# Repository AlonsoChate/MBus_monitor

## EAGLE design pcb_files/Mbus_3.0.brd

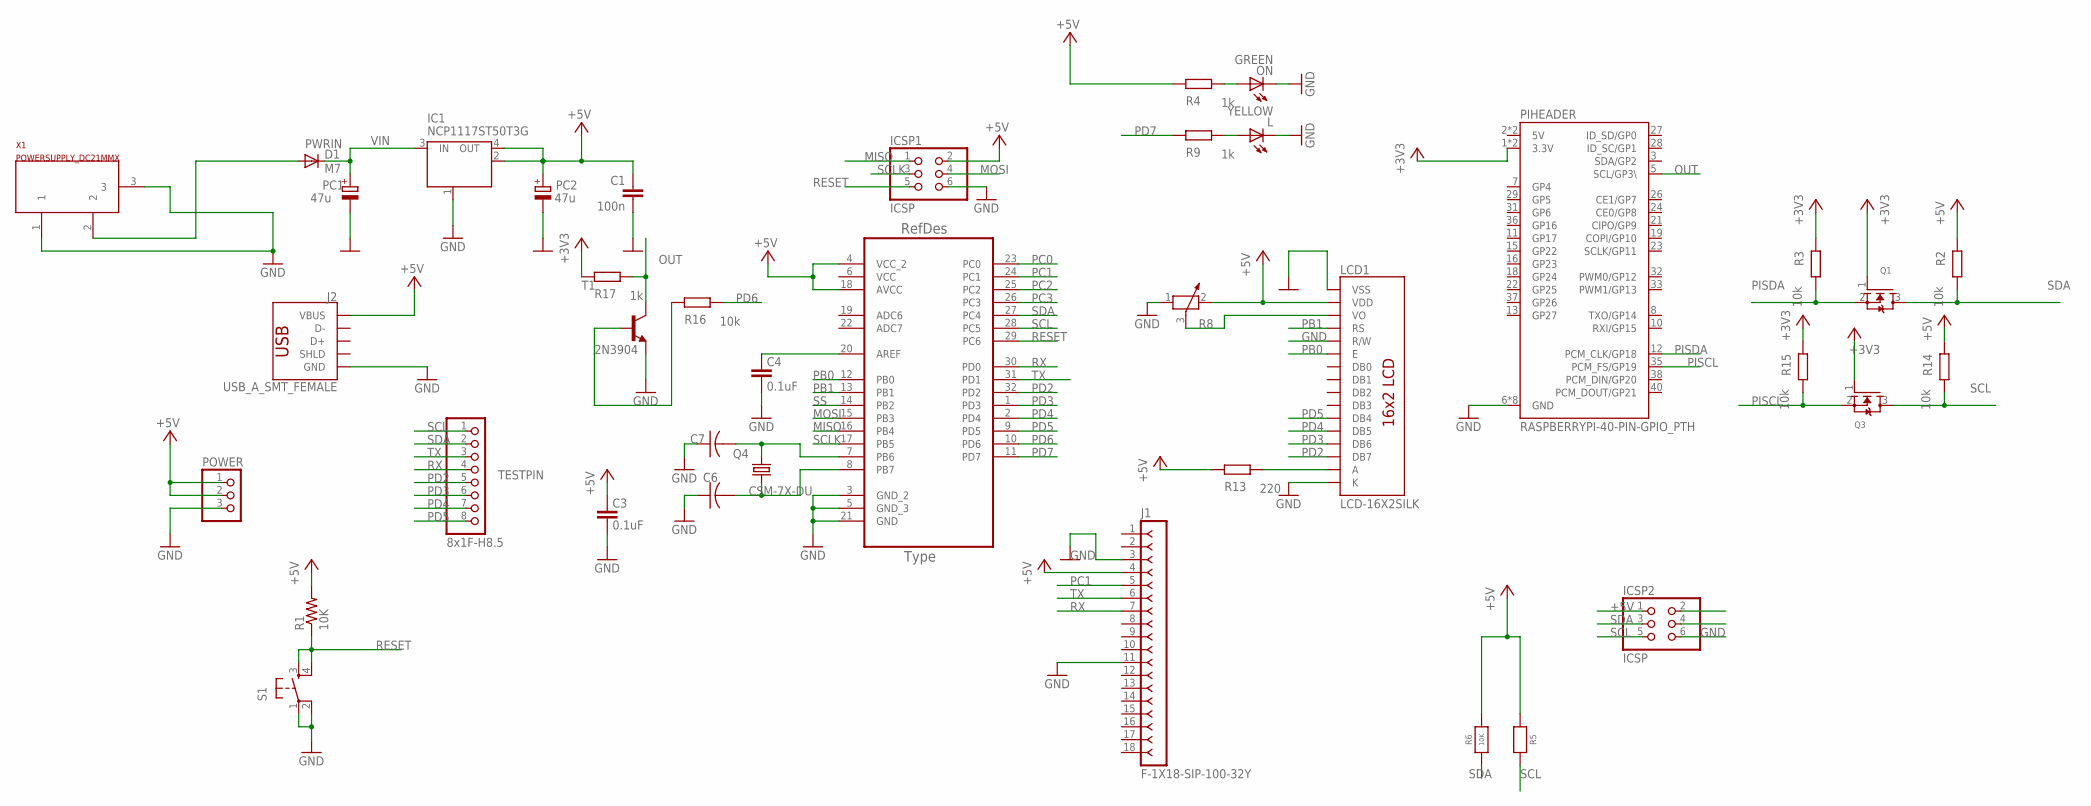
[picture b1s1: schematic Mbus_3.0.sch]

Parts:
C1: 100n; C0603-ROUND
C3, C4: 0.1uF; 0805
C6, C7: C-USC0805; C0805
D1: M7; SMB
IC1: NCP1117ST50T3G; SOT223
ICSP1, ICSP2: ICSP; 2X03
J1: F-1X18-SIP-100-32Y; SIP-100-18-32Y
J2: USB_A_SMT_FEMALE; USB-A-S-SILK-FEMALE
L: YELLOW; CHIP-LED0805
LCD1: LCD-16X2SILK; LCD-16X2
ON: GREEN; CHIP-LED0805
PC1, PC2: 47u; PANASONIC_D
PIHEADER: RASPBERRYPI-40-PIN-GPIO_PTH; 2X20_SHROUDED
POWER: PINHD-1X3; 1X03
Q1, Q3: BSS138; SOT23
Q4: CSM-7X-DU
R1: 10K; 0805
R2, R3, R14, R15, R16: 10k; R0603-ROUND
R4, R9, R17: 1k; R0603-ROUND
R5, R6: 10K; 0805-NO
R8: POTENTIOMETER_PT-10; PT-10
R13: 220; R0603-ROUND
S1: TAC_SWITCHPTH; TACTILE-PTH
T1: 2N3904; TO92
TESTPIN: 8x1F-H8.5; 1X08
U1: ATMEGA328P-AU; QFP80P900X900X120-32N
X1: POWERSUPPLY_DC21MMX; POWERSUPPLY_DC-21MM

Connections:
5V: PIHEADER.2 (5V), PIHEADER.4 (5V)
+3V3: PIHEADER.1 (3.3V), PIHEADER.17 (3.3V), Q1.1 (G), Q3.1 (G), R3.2, R15.2, R17.2
+5V: C1.1, C3.2, IC1.2 (OUT), IC1.4 (OUT), ICSP1.2, ICSP2.1, J1.4, J2.VBUS, LCD1.2 (VDD), PC2.+, POWER.1, POWER.2, R1.2, R2.2, R4.2, R5.1, R6.2, R8.2, R13.2, R14.2, U1.4 (VCC_2), U1.18 (AVCC)
GND: C1.2, C3.1, C4.1, C6.1, C7.1, IC1.1 (GND/ADJ), ICSP1.6, ICSP2.6, J1.3, J1.11, J2.GND, L.C, LCD1.1 (VSS), LCD1.5 (R/W), LCD1.16 (K), ON.C, PC1.-, PC2.-, PIHEADER.6 (GND), PIHEADER.9 (GND), PIHEADER.14 (GND), PIHEADER.20 (GND), PIHEADER.25 (GND), PIHEADER.30 (GND), PIHEADER.34 (GND), PIHEADER.39 (GND), POWER.3, R8.1, S1.1, S1.2, T1.3 (E), U1.3 (GND_2), U1.5 (GND_3), U1.21 (GND), X1.1, X1.3
MISO: ICSP1.1, U1.16 (PB4)
MOSI: ICSP1.4, U1.15 (PB3)
unnamed: C6.2, Q4.1, U1.8 (PB7)
unnamed: L.A, R9.1
unnamed: ON.A, R4.1
unnamed: R16.2, T1.2 (B)
unnamed: LCD1.15 (A), R13.1
unnamed: C7.2, Q4.2, U1.7 (PB6)
unnamed: C4.2, U1.20 (AREF)
unnamed: LCD1.3 (VO), R8.3
OUT: PIHEADER.5 (SCL/GP3\), R17.1, T1.1 (C)
PB0: LCD1.6 (E), U1.12 (PB0)
PB1: LCD1.4 (RS), U1.13 (PB1)
PC0: U1.23 (PC0)
PC1: J1.5, U1.24 (PC1)
PC2: U1.25 (PC2)
PC3: U1.26 (PC3)
PD2: LCD1.14 (DB7), TESTPIN.5, U1.32 (PD2)
PD3: LCD1.13 (DB6), TESTPIN.6, U1.1 (PD3)
PD4: LCD1.12 (DB5), TESTPIN.7, U1.2 (PD4)
PD5: LCD1.11 (DB4), TESTPIN.8, U1.9 (PD5)
PD6: R16.1, U1.10 (PD6)
PD7: R9.2, U1.11 (PD7)
PISCL: PIHEADER.35 (PCM_FS/GP19), Q3.2 (S), R15.1
PISDA: PIHEADER.12 (PCM_CLK/GP18), Q1.2 (S), R3.1
PWRIN: D1.A, X1.2
RESET: ICSP1.5, R1.1, S1.3, S1.4, U1.29 (PC6)
RX: J1.7, TESTPIN.4, U1.30 (PD0)
SCL: ICSP2.5, Q3.3 (D), R5.2, R14.1, TESTPIN.1, U1.28 (PC5)
SCLK: ICSP1.3, U1.17 (PB5)
SDA: ICSP2.3, Q1.3 (D), R2.1, R6.1, TESTPIN.2, U1.27 (PC4)
SS: U1.14 (PB2)
TX: J1.6, TESTPIN.3, U1.31 (PD1)
VCC: U1.6 (VCC)
VIN: D1.C, IC1.3 (IN), PC1.+

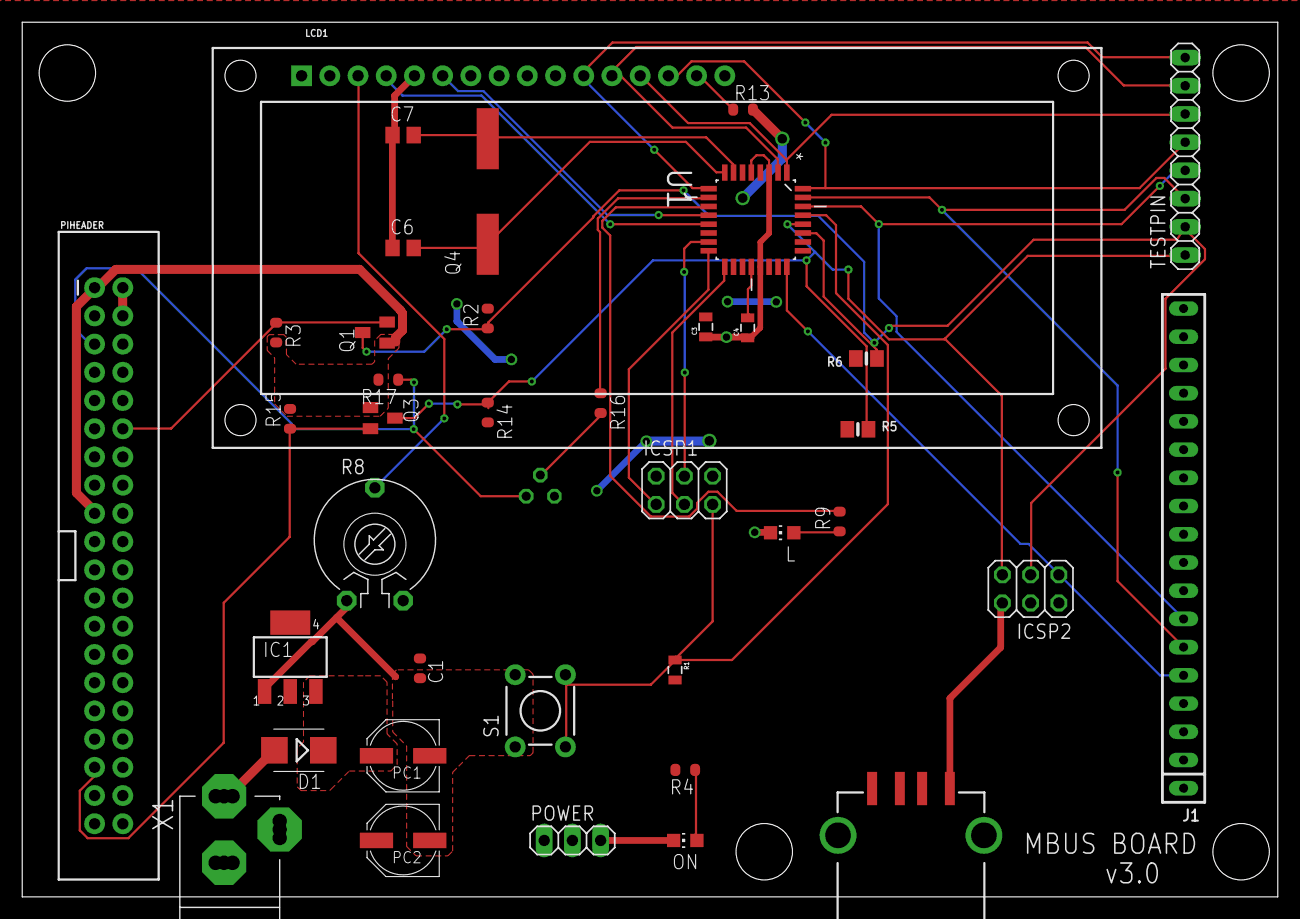
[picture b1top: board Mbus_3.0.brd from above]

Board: 2 copper layers, 113.0 x 78.7 mm, 39 parts (1 on the bottom side), 34 nets.

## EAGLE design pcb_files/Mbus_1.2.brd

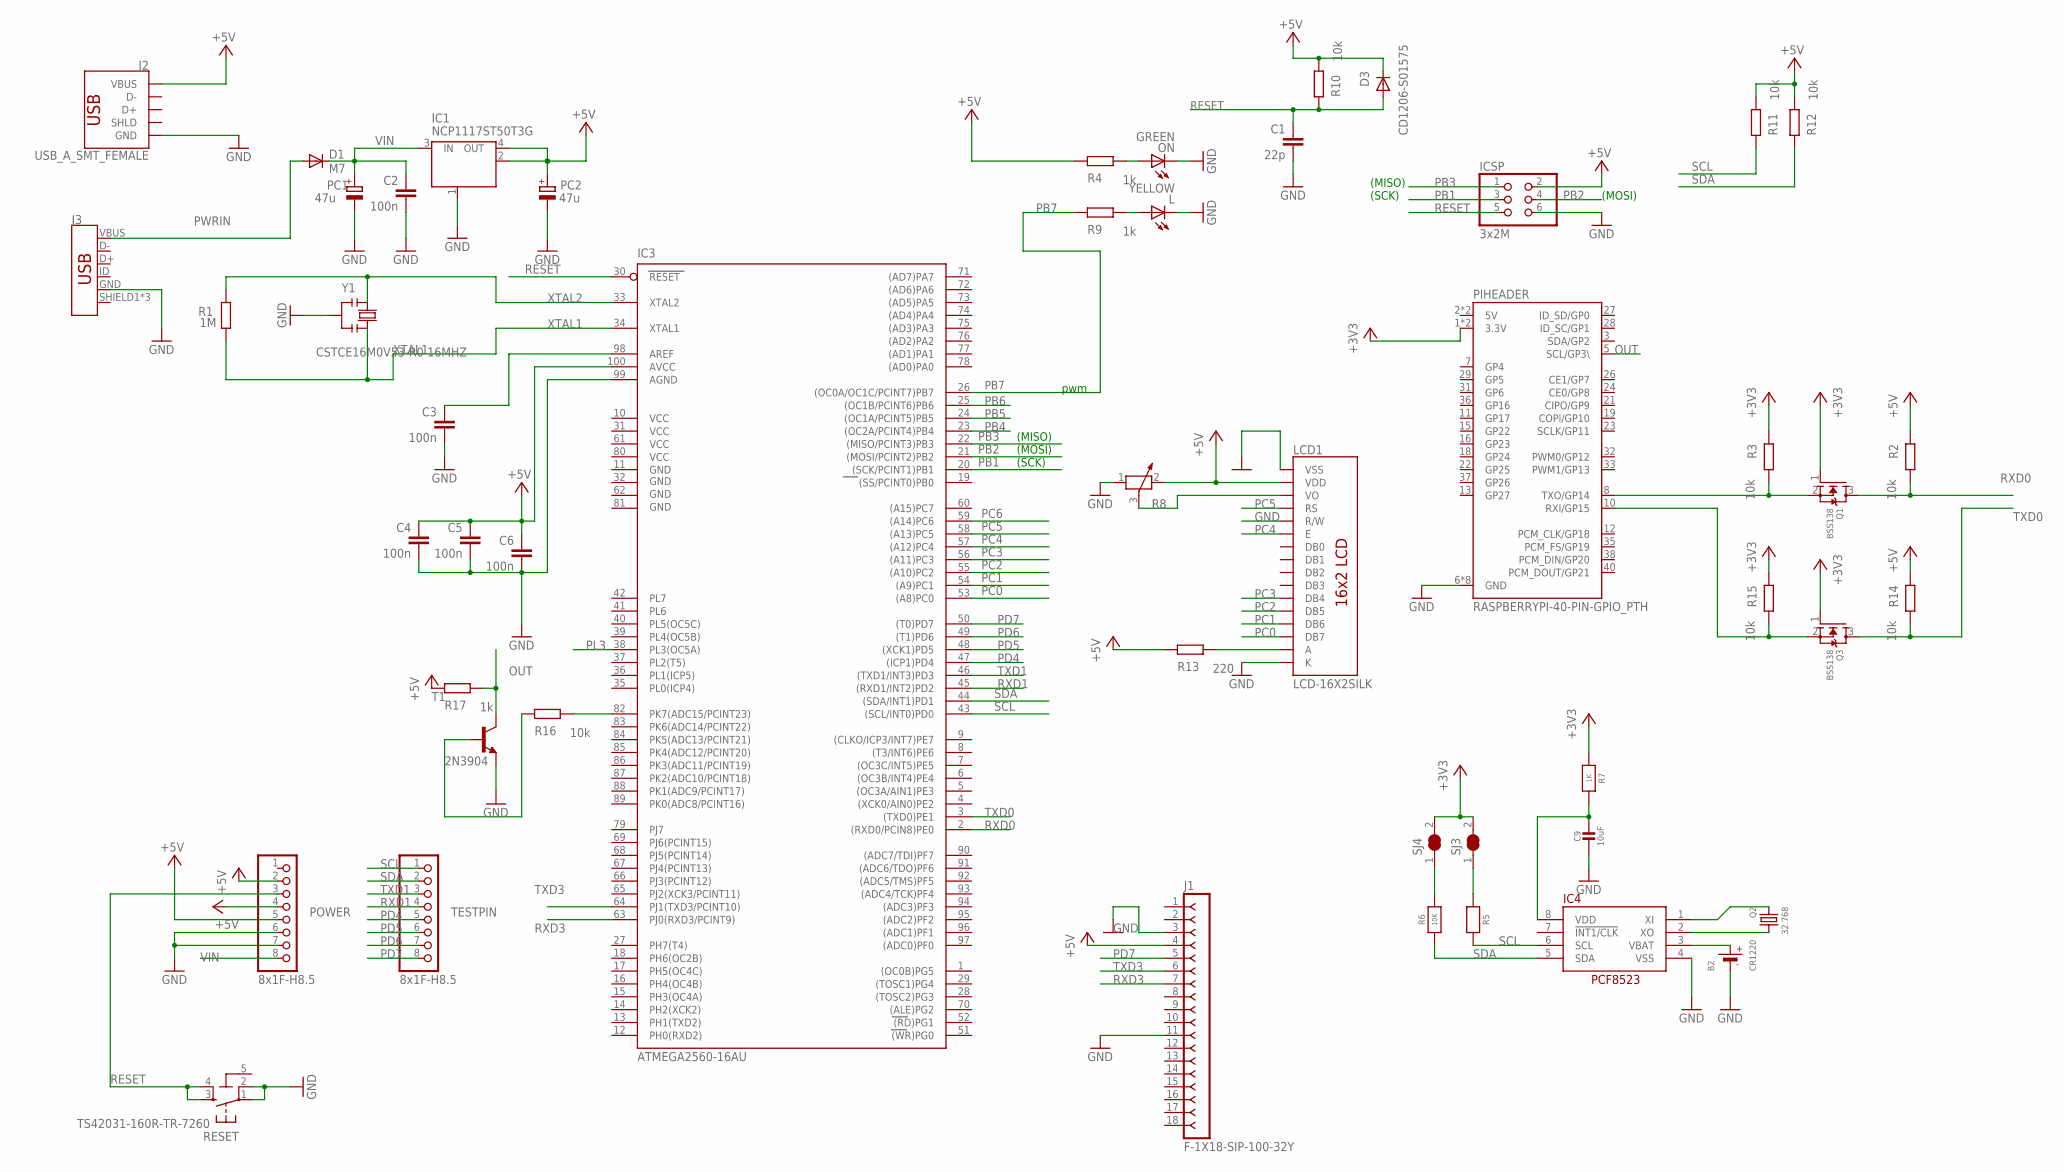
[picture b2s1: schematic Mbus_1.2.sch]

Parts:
B2: CR1220
C1: 22p; C0603-ROUND
C2, C3, C4, C5, C6: 100n; C0603-ROUND
C9: 10uF; 0805-NO
D1: M7; SMB
D3: CD1206-S01575; MINIMELF
IC1: NCP1117ST50T3G; SOT223
IC3: ATMEGA2560-16AU; TQFP100
IC4: RTC_PCF8523T; SOIC8_150MIL
ICSP: 3x2M; 2X03
J1: F-1X18-SIP-100-32Y; SIP-100-18-32Y
J2: USB_A_SMT_FEMALE; USB-A-S-SILK-FEMALE
J3: USB_MICRO-B_FEMALE-SMT; USB-B-MICRO-SMD
L: YELLOW; CHIP-LED0805
LCD1: LCD-16X2SILK; LCD-16X2
ON: GREEN; CHIP-LED0805
PC1, PC2: 47u; PANASONIC_D
PIHEADER: RASPBERRYPI-40-PIN-GPIO_PTH; 2X20_SHROUDED
POWER: 8x1F-H8.5; 1X08
Q1, Q3: BSS138; SOT23
Q2: 32.768; CRYSTAL_8X3.8
R1: 1M; R0603-ROUND
R2, R3, R10, R11, R12, R14, R15, R16: 10k; R0603-ROUND
R4, R9, R17: 1k; R0603-ROUND
R5, R6: 10K; 0805-NO
R7: 1K; 0805-NO
R8: POTENTIOMETER_PT-10; PT-10
R13: 220; R0603-ROUND
RESET: TS42031-160R-TR-7260; TS42
SJ3, SJ4: SOLDERJUMPER_CLOSED; SOLDERJUMPER_CLOSEDWIRE
T1: 2N3904; TO92
TESTPIN: 8x1F-H8.5; 1X08
Y1: CSTCE16M0V53-R0 16MHZ; RESONATOR

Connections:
5-GND: RESET.5 (5-GND)
5V: PIHEADER.2 (5V), PIHEADER.4 (5V)
+3V3: PIHEADER.1 (3.3V), PIHEADER.17 (3.3V), Q1.1 (G), Q3.1 (G), R3.2, R7.1, R15.2, SJ3.2, SJ4.2
+5V: C4.1, C5.1, C6.1, D3.C, IC1.2 (OUT), IC1.4 (OUT), IC3.100 (AVCC), ICSP.2, J1.4, J2.VBUS, LCD1.2 (VDD), PC2.+, POWER.2, POWER.4, POWER.5, R2.2, R4.2, R8.2, R10.1, R11.1, R12.1, R13.2, R14.2, R17.2
AREF: C3.1, IC3.98 (AREF)
GND: B2.-, C1.2, C2.2, C3.2, C4.2, C5.2, C6.2, C9.2, IC1.1 (GND/ADJ), IC3.11 (GND), IC3.99 (AGND), IC4.4 (VSS), ICSP.6, J1.3, J1.11, J2.GND, J3.GND, L.C, LCD1.1 (VSS), LCD1.5 (R/W), LCD1.16 (K), ON.C, PC1.-, PC2.-, PIHEADER.6 (GND), PIHEADER.9 (GND), PIHEADER.14 (GND), PIHEADER.20 (GND), PIHEADER.25 (GND), PIHEADER.30 (GND), PIHEADER.34 (GND), PIHEADER.39 (GND), POWER.6, POWER.7, R8.1, RESET.1, RESET.2, T1.3 (E), Y1.2
GND1: IC3.32 (GND1)
GND2: IC3.62 (GND2)
GND3: IC3.81 (GND3)
unnamed: IC3.82 (PK7(ADC15/PCINT23)), R16.1
unnamed: L.A, R9.1
unnamed: ON.A, R4.1
unnamed: R16.2, T1.2 (B)
unnamed: PIHEADER.8 (TXO/GP14), Q1.2 (S), R3.1
unnamed: IC4.1 (XI), Q2.P$1 (1)
unnamed: IC4.2 (XO), Q2.P$4 (2)
unnamed: R5.1, SJ3.1
unnamed: R6.2, SJ4.1
unnamed: C9.1, IC4.8 (VDD), R7.2
unnamed: LCD1.15 (A), R13.1
unnamed: PIHEADER.10 (RXI/GP15), Q3.2 (S), R15.1
unnamed: LCD1.3 (VO), R8.3
OUT: PIHEADER.5 (SCL/GP3\), R17.1, T1.1 (C)
PB1: IC3.20 ((SCK/PCINT1)PB1), ICSP.3
PB2: IC3.21 ((MOSI/PCINT2)PB2), ICSP.4
PB3: IC3.22 ((MISO/PCINT3)PB3), ICSP.1
PB4: IC3.23 ((OC2A/PCINT4)PB4)
PB5: IC3.24 ((OC1A/PCINT5)PB5)
PB6: IC3.25 ((OC1B/PCINT6)PB6)
PB7: IC3.26 ((OC0A/OC1C/PCINT7)PB7), R9.2
PC0: IC3.53 ((A8)PC0), LCD1.14 (DB7)
PC1: IC3.54 ((A9)PC1), LCD1.13 (DB6)
PC2: IC3.55 ((A10)PC2), LCD1.12 (DB5)
PC3: IC3.56 ((A11)PC3), LCD1.11 (DB4)
PC4: IC3.57 ((A12)PC4), LCD1.6 (E)
PC5: IC3.58 ((A13)PC5), LCD1.4 (RS)
PC6: IC3.59 ((A14)PC6)
PD4: IC3.47 ((ICP1)PD4), TESTPIN.5
PD5: IC3.48 ((XCK1)PD5), TESTPIN.6
PD6: IC3.49 ((T1)PD6), TESTPIN.7
PD7: IC3.50 ((T0)PD7), J1.5, TESTPIN.8
PL3: IC3.38 (PL3(OC5A))
PWRIN: D1.A, J3.VBUS
RESET: C1.1, D3.A, IC3.30 (RESET), ICSP.5, POWER.3, R10.2, RESET.3, RESET.4
RXD0: IC3.2 ((RXD0/PCIN8)PE0), Q1.3 (D), R2.1
RXD1: IC3.45 ((RXD1/INT2)PD2), TESTPIN.4
RXD3: IC3.63 (PJ0(RXD3/PCINT9)), J1.7
SCL: IC3.43 ((SCL/INT0)PD0), IC4.6 (SCL), R5.2, R11.2, TESTPIN.1
SDA: IC3.44 ((SDA/INT1)PD1), IC4.5 (SDA), R6.1, R12.2, TESTPIN.2
TXD0: IC3.3 ((TXD0)PE1), Q3.3 (D), R14.1
TXD1: IC3.46 ((TXD1/INT3)PD3), TESTPIN.3
TXD3: IC3.64 (PJ1(TXD3/PCINT10)), J1.6
VBAT1: B2.+$1 (+), IC4.3 (VBAT)
VCC: IC3.10 (VCC)
VCC1: IC3.31 (VCC1)
VCC2: IC3.61 (VCC2)
VCC3: IC3.80 (VCC3)
VIN: C2.1, D1.C, IC1.3 (IN), PC1.+, POWER.8
XTAL1: IC3.34 (XTAL1), R1.1, Y1.3
XTAL2: IC3.33 (XTAL2), R1.2, Y1.1

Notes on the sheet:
(SCK)
(MISO)
(MOSI)
pwm

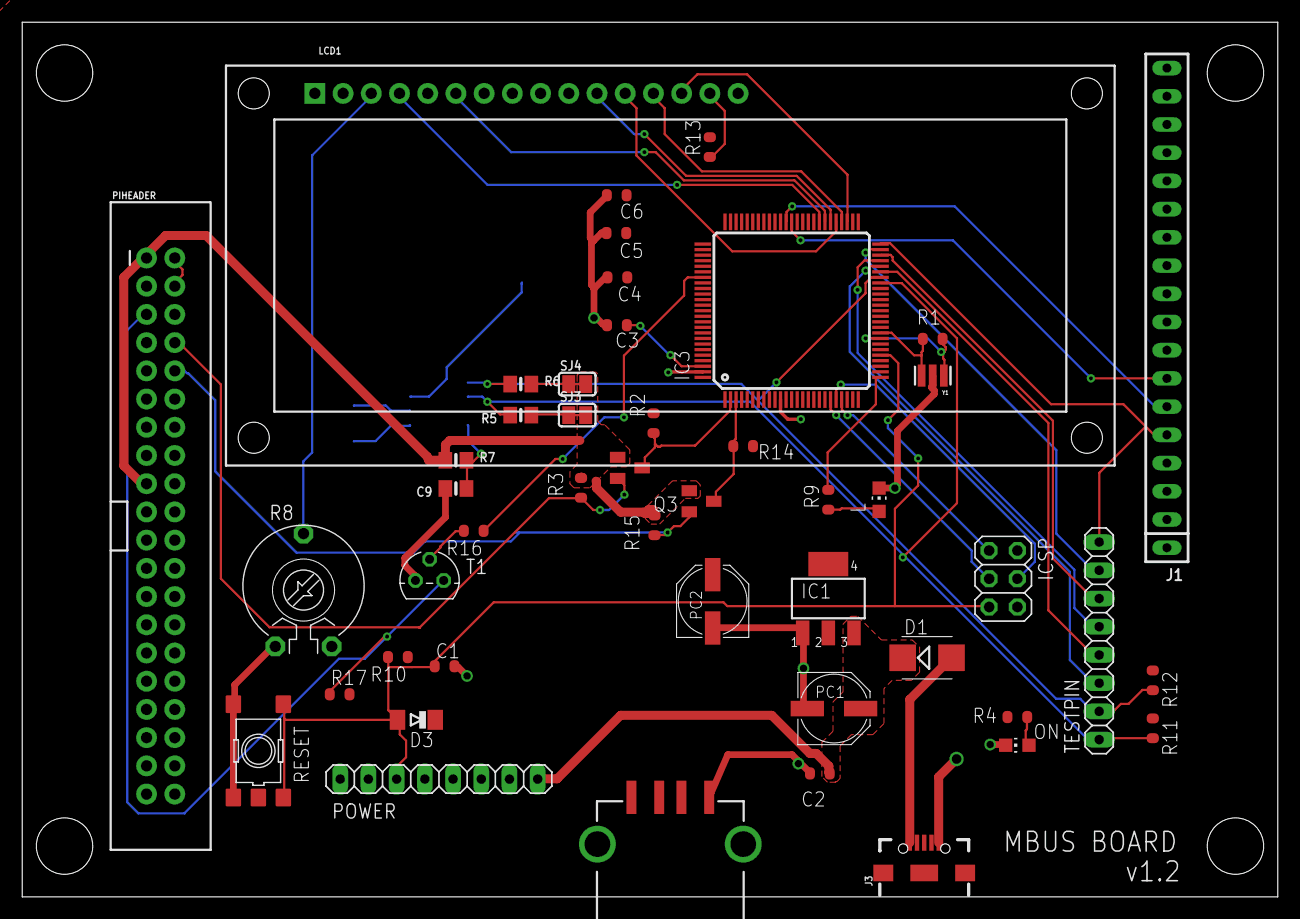
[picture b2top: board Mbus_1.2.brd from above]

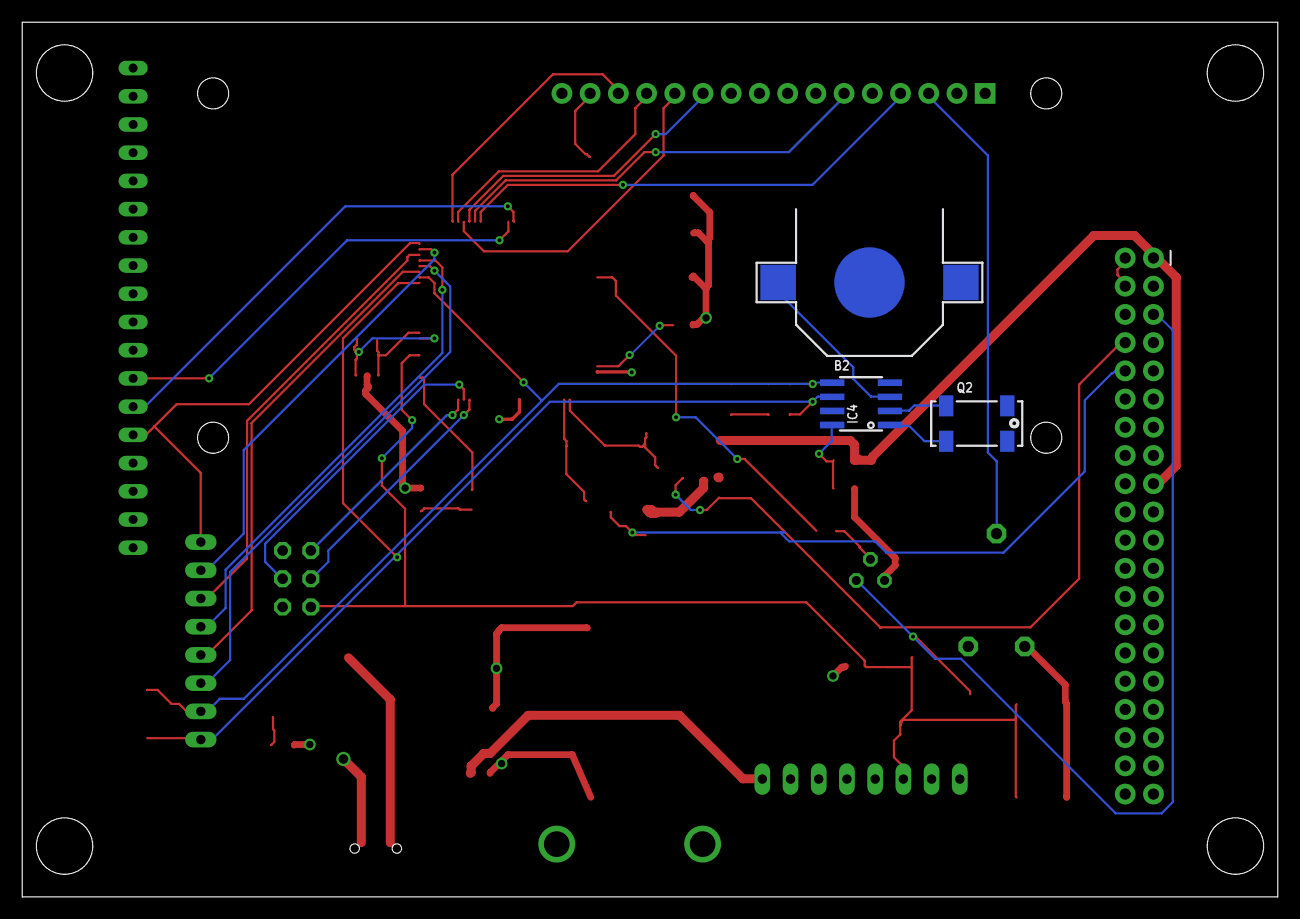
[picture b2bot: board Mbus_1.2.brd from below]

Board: 2 copper layers, 113.0 x 78.7 mm, 50 parts (3 on the bottom side), 47 nets.

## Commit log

2021-10-29 add pcb files
2021-10-30 Add resisters for 5V microcontroller to 3.3V pi pin header
2021-10-30 modify USB micro-B as power in and USB A port as output
2021-11-01 gpio re-organize
2021-11-01 route update
2021-11-02 A second version based on the previous one with similar layout.
2021-11-02 Fixed wire stubs
2021-11-02 Add modified Arduino Fona library
2021-11-03 Add the voltage level shifter circuit for uart in version 1.2.
2021-11-04 Modify direction of voltage level shifter
2021-11-04 Modify trace width based on Arduino mega.
2021-11-04 Connect RTC to Arduino and switch RTC power supply. Connect Arduino pin to Pi GPIO3 pin.
2021-11-05 Trial on polygon
2021-11-05 1.2 sch
2021-11-08 Modify the npn transistor and board layout for 1.2
2021-11-08 Modify trace width. Not finished on the board layout.
2021-11-09 fix the schematic issue of naming
2021-11-09 Add polygons
2021-11-09 Save
2021-11-09 Create gerber files
2021-11-10 Modify one trace
2021-11-10 final updates before submission
2021-11-11 board 2.0
2021-11-11 pcb layout of 2.0
2021-11-11 pcb 2.0
2021-11-11 Modify the traces and generate gerber file
2021-11-15 Add gsm code for testing
2021-11-19 connect lcd and gsm to arduino and finished initialization of gsm
2021-11-22 Write gsm version without RTOS.
2021-11-23 Fix bug on display.
2021-11-24 Change port number according to the pcb
2021-11-27 Switch to hardwareSerial for gsm communication.
2021-11-27 Add timer
2021-11-27 Add code for halt and wake up the pi
2021-11-27 rename
2021-11-28 Slight modification
2021-12-01 fix wake up issue.
2021-12-02 add arduino bus station code
2021-12-02 minor change
2021-12-02 modify arduino code wifi version
2021-12-02 modify gsm version to coincide with pi
2021-12-02 modify format of data post
2021-12-12 latest wifi

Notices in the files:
parts and their libraries:
microbuilder: This work is placed in the public domain, and may be freely used for commercial and non-commercial work with the following conditions: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
con-headers-jp: Copyright (C) 2008, Bob Starr
